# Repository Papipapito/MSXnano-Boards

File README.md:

# MSXnano · Boards

**Proof-of-concept carrier boards for the [MSXnano](https://github.com/Papipapito/MSXnano) project (Sipeed Tang Nano 20K).**
**Placas portadoras de prueba de concepto para el proyecto [MSXnano](https://github.com/Papipapito/MSXnano) (Sipeed Tang Nano 20K).**

*(English below · Español debajo)*

📄 Rich readme / readme enriquecido: [`README.html`](README.html)

### Gallery / Galería

| | |
|:---:|:---:|
|  |  |
| *Top-down 3D · Cenital 3D* | *Tang mounted on the socket · Tang montado en el zócalo* |
|  |  |
| *Assembled · Montado* | *Top copper in KiCad (routing) · Cobre superior en KiCad (rutado)* |

More views in [`dock20k/`](dock20k/): full-res renders, front elevation, bottom copper, schematic & PCB PDFs.
*Más vistas en [`dock20k/`](dock20k/): renders a resolución completa, alzado frontal, cobre inferior, PDFs de esquemático y PCB.*

---

## 🇬🇧 English

These are **proof-of-concept boards built around the Sipeed M0S (BL616)** module. They exist for one exact reason:

> Since **~February 2024**, Sipeed ships Tang Nano 20K boards (silk-marked **`3921`**) whose **on-board BL616** has its **secure-boot eFuse in a state that often prevents it from running the FPGA-Companion firmware**. When that happens, the **USB keyboard and mouse stop working** (HDMI and the on-screen menu still work — that part is the FPGA, not the BL616). Sipeed's official workaround is to use an **external M0S Dock**.

Instead of hanging an external dock off the board with loose wires, these boards **integrate a dedicated M0S (BL616)** as the USB companion — plus a USB hub and WiFi — onto a single carrier, so **everything runs through the Tang's 2×20 headers with no external cables**.

### Boards

| Board | What it is | Status |
|-------|------------|--------|
| [**dock20k**](dock20k/) | Tang Nano 20K carrier: **M0S (BL616)** companion + **FE1.1s** 4-port USB hub (2×USB-A + 2×USB-C) + **ESP32-C6** WiFi (UNAPI). Single USB-C power in. | Schematic ERC 0 · PCB routed (DRC 0) · **not yet fabricated** |
| [**rpi3-compatible**](rpi3-compatible/) | **Raspberry Pi 3 form factor (85×56 mm, 4-layer).** Fully modular: plug-in **Raspberry Pi Pico (RP2040)** USB companion + **ESP-01S** WiFi + **FE1.1s** hub. No soldered BL616/ESP32 — nothing exotic to source. | PCB routed (DRC 0 electrical) · **JLCPCB fab package ready** · not fabricated |

### rpi3-compatible highlights

- **Plug-in Raspberry Pi Pico (RP2040)** as the USB-HID companion, running the FPGA-Companion **`PICO`** build over the same `m0s[]` SPI path — **no RTL changes**, and it sidesteps the Tang `3921` BL616 secure-boot issue entirely (there is no on-board BL616).
- **ESP-01S** for WiFi on the core's **859372 bps** UART. Both the Pico and the ESP are **modules on sockets** — trivial to source, replace, or reflash.
- **Raspberry Pi 3 outline** (85 × 56 mm, RPi3 mounting pattern), **4 copper layers**, routed 100 % with GND planes. Ships with a **complete JLCPCB fab package** (gerbers + BOM + CPL, rotation-corrected).
- Details & key parts: [`rpi3-compatible/README.md`](rpi3-compatible/README.md).

### dock20k highlights

- **M0S (BL616)** runs the stock [FPGA-Companion](https://github.com/MiSTle-Dev/FPGA-Companion) `M0S_DOCK` build over the external `m0s[]` SPI path — **no RTL changes** to the MSXnano core.
- **ESP32-C6-WROOM-1-N8** for internet, running ducasp's [ESP32-UNAPI firmware](https://github.com/ducasp/ESP32-UNAPI-Firmware). It's the C6 (not the classic WROOM) because the core fixes the WiFi UART at **859372 bps**, a rate that is unreliable on the WROOM but fine on the C6.
- Everything routed through the **Tang's own 2×20 headers** — no external cables. Free Tang pins are broken out on an expansion header for future add-ons (e.g. MSX-MIDI).
- Connector & jumper reference: [`dock20k/CONNECTORS.md`](dock20k/CONNECTORS.md).

> ⚠️ **Proof of concept.** Designed and routed in KiCad but **not manufactured or tested in hardware yet.** Before ordering, verify the Tang socket against a physical board (rows at 20.32 mm, pin-1 position).

---

## 🇪🇸 Español

Estas son **placas de prueba de concepto construidas alrededor del módulo Sipeed M0S (BL616)**. Existen por una razón exacta:

> Desde **~febrero de 2024**, Sipeed fabrica placas Tang Nano 20K (marcadas **`3921`** en la serigrafía) cuyo **BL616 de a bordo** tiene el eFuse de **secure-boot en un estado que a menudo le impide ejecutar el firmware FPGA-Companion**. Cuando eso pasa, **el teclado y el ratón USB dejan de funcionar** (el HDMI y el menú en pantalla sí van — eso lo hace la FPGA, no el BL616). La solución oficial de Sipeed es usar un **M0S Dock externo**.

En lugar de colgar un dock externo con cables sueltos, estas placas **integran un M0S (BL616) dedicado** como companion USB —además de un hub USB y WiFi— en una sola portadora, de modo que **todo funciona por los conectores 2×20 del Tang, sin cables externos**.

### Placas

| Placa | Qué es | Estado |
|-------|--------|--------|
| [**dock20k**](dock20k/) | Portadora del Tang Nano 20K: companion **M0S (BL616)** + hub USB **FE1.1s** de 4 puertos (2×USB-A + 2×USB-C) + WiFi **ESP32-C6** (UNAPI). Entrada única de 5 V por USB-C. | Esquemático ERC 0 · PCB rutada (DRC 0) · **sin fabricar aún** |
| [**rpi3-compatible**](rpi3-compatible/) | **Formato Raspberry Pi 3 (85×56 mm, 4 capas).** Totalmente modular: **Raspberry Pi Pico (RP2040)** enchufable como companion USB + **ESP-01S** WiFi + hub **FE1.1s**. Sin BL616/ESP32 soldados — nada raro que abastecer. | PCB rutada (DRC 0 eléctricos) · **paquete de fabricación JLCPCB listo** · sin fabricar |

### Claves de rpi3-compatible

- **Raspberry Pi Pico (RP2040) enchufable** como companion USB-HID, con el build **`PICO`** de FPGA-Companion por la misma ruta SPI `m0s[]` — **sin tocar el RTL**, y esquiva por completo el problema del secure-boot del BL616 de los Tang `3921` (aquí no hay BL616).
- **ESP-01S** para WiFi en la UART del core a **859372 bps**. Tanto el Pico como el ESP son **módulos en zócalos** — fáciles de abastecer, sustituir o reflashear.
- **Contorno Raspberry Pi 3** (85 × 56 mm, patrón de anclajes RPi3), **4 capas de cobre**, rutada al 100 % con planos de GND. Incluye un **paquete de fabricación JLCPCB completo** (gerbers + BOM + CPL, con rotaciones corregidas).
- Detalles y piezas clave: [`rpi3-compatible/README.md`](rpi3-compatible/README.md).

### Claves de dock20k

- El **M0S (BL616)** ejecuta el build `M0S_DOCK` de [FPGA-Companion](https://github.com/MiSTle-Dev/FPGA-Companion) tal cual, por la ruta SPI externa `m0s[]` — **sin tocar el RTL** del core MSXnano.
- **ESP32-C6-WROOM-1-N8** para internet, con el [firmware ESP32-UNAPI](https://github.com/ducasp/ESP32-UNAPI-Firmware) de ducasp. Es el C6 (no el WROOM clásico) porque el core fija la UART del WiFi a **859372 bps**, una velocidad poco fiable en el WROOM pero correcta en el C6.
- Todo enrutado por los **conectores 2×20 del propio Tang** — sin cables externos. Los pines libres del Tang salen a un cabezal de expansión para futuras ampliaciones (p. ej. MSX-MIDI).
- Referencia de conectores y jumpers: [`dock20k/CONNECTORS.md`](dock20k/CONNECTORS.md).

> ⚠️ **Prueba de concepto.** Diseñada y rutada en KiCad pero **aún no fabricada ni probada en hardware.** Antes de encargarla, verifica el zócalo del Tang contra una placa física (filas a 20.32 mm, posición del pin 1).

---

### Credits / Créditos

Board design: **Papipapito**. Third-party footprints/3D models (Sipeed M0S, Espressif ESP32-C6) keep their own licenses. BL616 firmware: [FPGA-Companion](https://github.com/MiSTle-Dev/FPGA-Companion) (MiSTle-Dev). WiFi firmware: [ESP32-UNAPI](https://github.com/ducasp/ESP32-UNAPI-Firmware) (ducasp).

*Diseño de la placa: **Papipapito**. Las huellas/modelos 3D de terceros conservan su licencia. Firmware BL616: FPGA-Companion. Firmware WiFi: ESP32-UNAPI de ducasp.*

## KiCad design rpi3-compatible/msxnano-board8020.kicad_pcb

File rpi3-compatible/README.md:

# rpi3-compatible

**MSXnano carrier in Raspberry Pi 3 form factor (85 × 56 mm), fully modular.**
**Placa portadora MSXnano con formato Raspberry Pi 3 (85 × 56 mm), totalmente modular.**

Instead of soldering the USB companion and WiFi chips (like [`../dock20k`](../dock20k/)), this board takes **plug-in modules**: a **Raspberry Pi Pico (RP2040)** as the USB-HID companion and an **ESP-01S** for WiFi — so there is nothing exotic to source or reflow, and the RPi3 outline drops into any Pi-3 case/mount.

En lugar de soldar los chips de companion USB y WiFi (como en [`../dock20k`](../dock20k/)), esta placa usa **módulos enchufables**: una **Raspberry Pi Pico (RP2040)** como companion USB-HID y un **ESP-01S** para WiFi — así no hay nada raro que abastecer ni soldar, y el contorno RPi3 encaja en cualquier caja/soporte de Pi 3.

### Views / Vistas

| | |
|:---:|:---:|
|  |  |
| *3D top (as placed) · 3D cenital (colocación real)* | *4-layer routing · Rutado 4 capas* |

PDFs: [schematic](board8020_schematic.pdf) · [PCB top](board8020_pcb_top.pdf) · 3D: [`board8020_rpi3.step`](board8020_rpi3.step)

```
USB-C 5V ──fuse 2A──► +5V ──► Tang 5V (socket) + Pico VSYS
                       ├──► AMS1117-3.3 ──► ESP-01S (WiFi)
                       └──► FE1.1s hub ──► 4 downstream ports (500 mA polyfuse each)

Tang (2x20 socket) ──SPI (M0S_* nets)──► RPi Pico (FPGA-Companion PICO build) ──USB host──► FE1.1s hub ──► 2×USB-A + USB2 header
                   ──UART 27/28──► ESP-01S UART @ 859372 bps
Pico GP20 ──► WS2812 header (J8, DIN)
```

## EN — Design notes

- **USB companion = plug-in Raspberry Pi Pico (RP2040)** on a 2×20 female socket, running the FPGA-Companion **`PICO`** build (PIO-USB host). Drives keyboard/mouse/joystick over the same SPI `m0s[]` path the core already detects — **no RTL changes**. Avoids the Tang `3921` BL616 secure-boot problem entirely (no on-board BL616 involved).
- **WiFi = ESP-01S** on a 2×4 female socket, on the core's WiFi UART @ **859372 bps** (its own 3.3 V LDO + pull-ups).
- **Hub = FE1.1s** (SSOP-28) with a **12 MHz SMD-3225 crystal** (JLC Basic C9002). Downstream: 2× USB-A on the rear edge + a **2×5 USB2 header** (2 more ports).
- **Form factor:** exact **Raspberry Pi 3** outline — 85 × 56 mm, 4 mounting holes on the RPi3 58 × 49 pattern. **4 copper layers.**
- **Header-only parts:** the USB2 header (J6), the ESP-01 socket (J7) and the **WS2812 3-pin header (J8)** are left as **plated holes** — solder your own. They are **excluded from the assembly BOM**.

## ES — Notas de diseño

- **Companion USB = Raspberry Pi Pico (RP2040) enchufable** en zócalo 2×20 hembra, con el build **`PICO`** de FPGA-Companion (host USB por PIO). Lleva teclado/ratón/joystick por la misma ruta SPI `m0s[]` que el core ya detecta — **sin tocar el RTL**. Evita por completo el problema del secure-boot del BL616 de los Tang `3921` (aquí no hay BL616).
- **WiFi = ESP-01S** en zócalo 2×4 hembra, en la UART de WiFi del core a **859372 bps** (con su LDO de 3.3 V y pull-ups).
- **Hub = FE1.1s** (SSOP-28) con **cristal 12 MHz SMD-3225** (JLC Basic C9002). Downstream: 2× USB-A en el borde trasero + un **header USB2 2×5** (2 puertos más).
- **Formato:** contorno exacto de **Raspberry Pi 3** — 85 × 56 mm, 4 anclajes en el patrón RPi3 58 × 49. **4 capas de cobre.**
- **Piezas solo-agujeros:** el header USB2 (J6), el zócalo del ESP-01 (J7) y el **header WS2812 de 3 pines (J8)** quedan como **agujeros metalizados** — los sueldas tú. Están **fuera del BOM de montaje**.

## Status / Estado

- EN: 85 × 56 mm **4-layer PCB, routed 100 %** with freerouting, GND planes on all 4 layers. **DRC: 0 unconnected, 0 electrical errors** (only cosmetic silk/library warnings). **JLCPCB fabrication package included** (gerbers + BOM + CPL). Component placement done by hand. **Not fabricated yet** — before ordering, verify the USB-A (J1/J2) and USB-C (J3) footprints/orientation and the Pico/Tang socket rows against physical modules.
- ES: PCB de **4 capas 85 × 56 mm, rutada al 100 %** con freerouting, planos de GND en las 4 capas. **DRC: 0 sin conectar, 0 errores eléctricos** (solo avisos cosméticos de serigrafía/librería). **Paquete de fabricación JLCPCB incluido** (gerbers + BOM + CPL). Colocación de componentes hecha a mano. **Sin fabricar aún** — antes de encargarla, verifica los footprints/orientación de los USB-A (J1/J2) y USB-C (J3) y las filas de los zócalos Pico/Tang contra los módulos físicos.

## Files / Ficheros

`msxnano-board8020.kicad_pro/.kicad_sch/.kicad_pcb` · `sym-lib-table` / `fp-lib-table` (paths via `${KIPRJMOD}`) · `libs/` (M0S + Espressif symbols/footprints/3D, FE1.1s + Tang/Pico sockets custom) · `board8020_schematic.pdf` · `board8020_pcb_top.pdf` · `board8020_rpi3.step` · **fab:** `board8020_gerbers.zip` · `board8020_BOM_jlcpcb.csv` · `board8020_CPL_jlcpcb.csv` (JLCPCB format, top side, rotation-corrected).

## Key parts / Piezas clave (JLCPCB LCSC)

FE1.1s hub `C9359` (SSOP-28) · AMS1117-3.3 `C6186` · USBLC6-2SC6 ESD `C2687116` ×4 · 12 MHz 3225 xtal `C9002` (Basic) · SMAJ5.0A TVS `C2925443` · USB-C `C165948` · USB-A horiz `C2345` ×2 · 10k `C98220` · 5.1k `C23186` · 2.7k `C13167` · PPTC 2A `C960026` / 500mA `C369168`. **Not assembled (holes only):** RPi Pico, Tang Nano 20K, ESP-01S socket, USB2 header, WS2812 header.

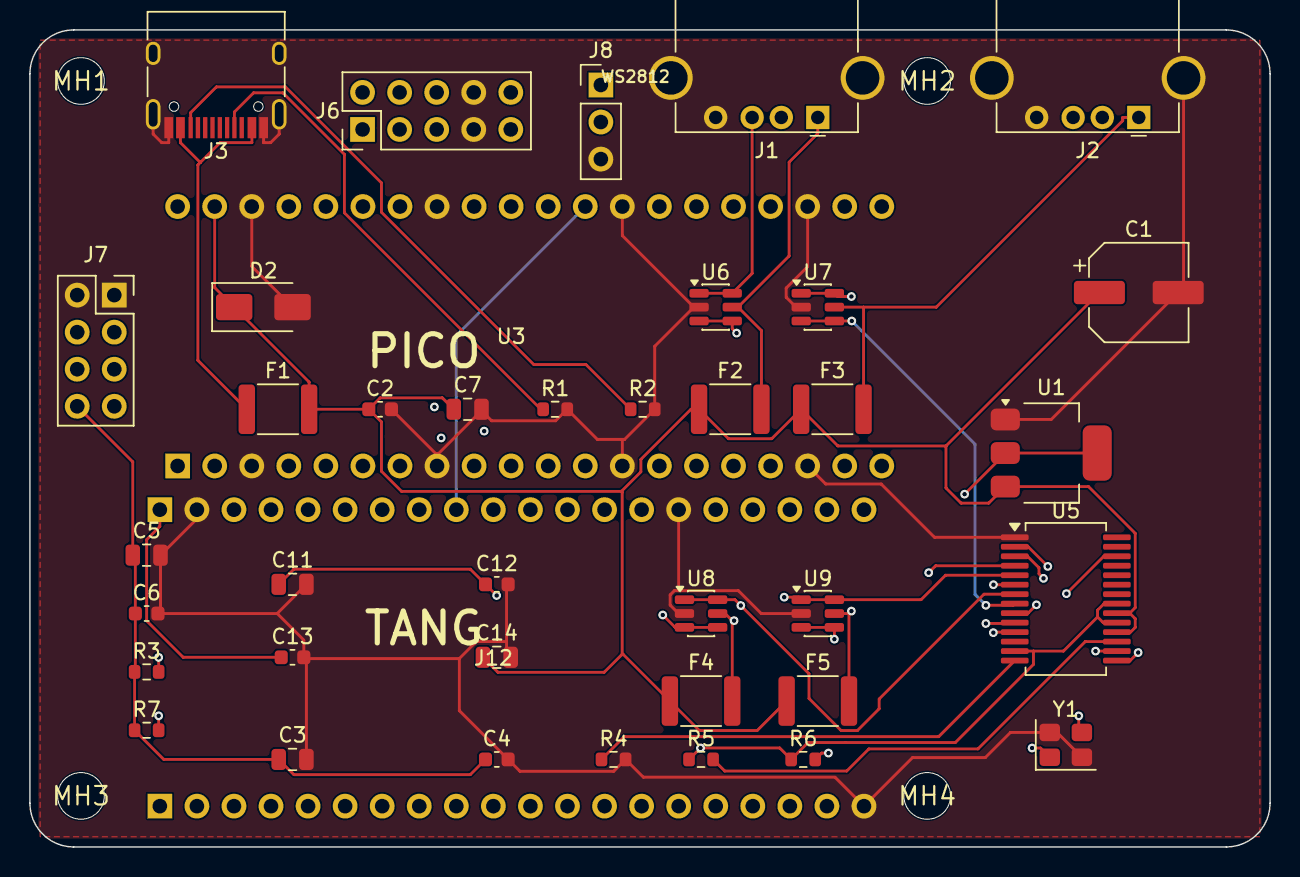
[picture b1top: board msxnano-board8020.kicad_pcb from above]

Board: 4 copper layers, 85.0 x 56.0 mm, 43 parts (0 on the bottom side), 37 nets.

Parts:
C1: 220uF/10V; CP_Elec_6.3x7.7
C2, C4, C6, C12, C13: 100nF; C_0603_1608Metric
C3: 22uF; C_0805_2012Metric
C5, C7, C11, C14: 10uF; C_0805_2012Metric
D2: SMAJ5.0A; D_SMA
F1: 2A; Fuse_1812_4532Metric
F2, F3, F4, F5: 500mA; Fuse_1812_4532Metric
J1: USB-A_front1; USB_A_Stewart_SS-52100-001_Horizontal
J2: USB-A_front2; USB_A_Stewart_SS-52100-001_Horizontal
J3: USB-C_power_in; USB_C_Receptacle_HRO_TYPE-C-31-M-12
J6: USB2.0_Header; PinHeader_2x05_P2.54mm_Vertical
J7: ESP-01S; PinSocket_2x04_P2.54mm_Vertical
J8: WS2812; PinHeader_1x03_P2.54mm_Vertical
J12: TangNano20K; TangNano20K_Socket
MH1, MH2, MH3, MH4: MountingHole_3.2mm
R1, R2: 5k1; R_0603_1608Metric
R3, R5, R6, R7: 10k; R_0603_1608Metric
R4: 2k7 1%; R_0603_1608Metric
U1: AMS1117-3.3; SOT-223-3_TabPin2
U3: RaspberryPi_Pico; RPi_Pico_Socket
U5: FE1.1s; SSOP-28_5.3x10.2mm_P0.65mm
U6, U7, U8, U9: USBLC6-2SC6; SOT-23-6
Y1: 12MHz; Crystal_SMD_3225-4Pin_3.2x2.5mm

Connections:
+3V3_ESP: C3.1, C4.1, C5.1, C6.1, J7.6, J7.8, R3.1, R7.1, U1.2
+3V3_HUB: C11.1, C12.1, R5.1, R6.1, U5.13, U5.19, U5.21
+5V: C1.1, C2.1, C7.1, C13.1, C14.1, D2.1, F1.2, F2.1, F3.1, F4.1, F5.1, J8.1, J12.A1, U1.3, U3.39, U3.40, U5.18, U5.20
BL_USB_DM: U3.5, U5.15
BL_USB_DP: U3.4, U5.16
CC1: J3.A5, R1.1
CC2: J3.B5, R2.1
ESP_GPIO0: J7.3, R3.2
ESP_RST: J7.7, R7.2
ESP_RX0: J7.4, J12.B8
ESP_TX0: J7.5, J12.B9
GND: C1.2, C2.2, C3.2, C4.2, C5.2, C6.2, C7.2, C11.2, C12.2, C13.2, C14.2, D2.2, J1.4, J1.5, J2.4, J2.5, J3.A1, J3.A12, J3.B1, J3.B12, J3.S1, J6.7, J6.8, J7.1, J7.2, J8.3, J12.A2, J12.A15, J12.B20, R1.2, R2.2, R4.2, U1.1, U3.3, U3.8, U3.13, U3.18, U3.23, U3.28, U3.33, U3.38, U5.1, U6.2, U7.2, U8.2, U9.2, Y1.2, Y1.4
HUB_OVCJ: R6.2, U5.26
HUB_REXT: R4.1, U5.14
HUB_RSTJ: R5.2, U5.17
HUB_XIN: U5.3, Y1.1
HUB_XOUT: U5.2, Y1.3
M0S_CSN: J12.A7, U3.22
M0S_IRQ: J12.A9, U3.29
M0S_MISO: J12.A5, U3.21
M0S_MOSI: J12.A6, U3.25
M0S_SCK: J12.A8, U3.24
P1_DM: J1.2, U5.10, U6.3, U6.4
P1_DP: J1.3, U5.11, U6.1, U6.6
P2_DM: J2.2, U5.8, U7.3, U7.4
P2_DP: J2.3, U5.9, U7.1, U7.6
P3_DM: J6.3, U5.6, U8.3, U8.4
P3_DP: J6.5, U5.7, U8.1, U8.6
P4_DM: J6.4, U5.4, U9.3, U9.4
P4_DP: J6.6, U5.5, U9.1, U9.6
TANG_3V3: J12.A16, J12.B19
USB5V_P1: F2.2, J1.1, U6.5
USB5V_P2: F3.2, J2.1, U7.5
USB5V_P3: F4.2, J6.1, U8.5
USB5V_P4: F5.2, J6.2, U9.5
VBUS_IN: F1.1, J3.A4, J3.A9, J3.B4, J3.B9
WS2812_DIN: J8.2, U3.26

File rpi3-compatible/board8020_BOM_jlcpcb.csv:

Comment,Designator,Footprint,LCSC Part #
5.1k 0603 1%,"R1,R2",R_0603,C23186
10k 0603 1%,"R3,R5,R6,R7",R_0603,C98220
2.7k 0603 1%,R4,R_0603,C13167
100nF 50V 0603,"C2,C4,C6,C12,C13",C_0603,C14663
10uF 25V 0805,"C5,C7,C11,C14",C_0805,C15850
22uF 25V 0805,C3,C_0805,C45783
220uF 25V,C1,CP_Elec_6.3x7.7,C2918361
12MHz,Y1,Crystal_SMD_3225-4Pin,C9002
AMS1117-3.3,U1,SOT-223,C6186
FE1.1S,U5,SSOP-28,C9359
USBLC6-2SC6,"U6,U7,U8,U9",SOT-23-6,C2687116
SMAJ5.0A,D2,D_SMA,C2925443
PPTC 2A,F1,Fuse_1812,C960026
PPTC 500mA,"F2,F3,F4,F5",Fuse_1812,C369168
USB-C TYPE-C-31-M-12,J3,USB_C_HRO,C165948
USB-A hembra horiz 902-131A,"J1,J2",USB_A_horiz,C2345

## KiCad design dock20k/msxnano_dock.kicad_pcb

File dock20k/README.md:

# dock20k

Carrier / dock board for the **Tang Nano 20K** running the **MSXnano** core.
Placa portadora ("dock") para el **Tang Nano 20K** con el core **MSXnano**.

📖 See [`CONNECTORS.md`](CONNECTORS.md) for the full connector/jumper reference · [`../README.html`](../README.html) for the illustrated bilingual overview.

### Views / Vistas

| | |
|:---:|:---:|
|  |  |
| *Top-down 3D · Cenital 3D* | *Tang on socket · Tang en zócalo* |
|  |  |
| *Top copper routing (KiCad) · Rutado cobre superior* | *Front elevation of the stack · Alzado del stack* |

Full-res: [`render_top.png`](render_top.png) · [`render_iso_ports.png`](render_iso_ports.png) · [`render_dock.png`](render_dock.png) · [`layout_top.png`](layout_top.png) · [`layout_bottom.png`](layout_bottom.png) · PDFs: [schematic](msxnano_dock_schematic.pdf) · [PCB top](msxnano_dock_pcb_top.pdf) / [bottom](msxnano_dock_pcb_bottom.pdf)

```
USB-C 5V ──fuse 2A──► +5V ──SS34──► Tang 5V pin (J5.1)
                       ├──► AMS1117-3.3 #1 ──► ESP32-C6
                       ├──► AMS1117-3.3 #2 ──► M0S / BL616
                       └──► FE1.1s hub + 4 ports (500 mA polyfuse each)

Tang (2x20 socket) ──SPI 42/41/56/54/51──► M0S BL616 ──USB──► FE1.1s hub ──► 2×USB-A + 2×USB-C
                   ──UART 27/28──► ESP32-C6 UART0 @ 859372 bps
                   ──pin 25──► WS2812   ──pins 15-20──► status LEDs   ──pin 26──► ESP reset (R20 0Ω)
```

## EN — Design notes

- **BL616 = bare Sipeed M0S module** (soldered). Runs the stock FPGA-Companion `M0S_DOCK` build — SPI on IO10–IO14 exactly like the dock, detected by the core via `m0s[2]`. No RTL changes. The M0S has **no on-board regulator** → dedicated 3.3 V LDO.
- **Hub = FE1.1s** (SSOP-28): 12 MHz crystal (load caps integrated), REXT 2.7 kΩ 1%, self-powered (BUSJ→3V3, **OVCJ→10k to 3V3, mandatory**, PWRJ NC). Note: the Rev 1.0 datasheet misprints DMU as pin 25 — it is **pin 15**.
- **WiFi = ESP32-C6-WROOM-1-N8** with ducasp's ESP32-UNAPI firmware. The core's WiFi UART is fixed at **859372 bps**; ducasp reports that rate is unreliable on the classic WROOM but fine on the C6 (the repo's default target). Needs **8 MB flash** → the -N8 part.
- **Rule:** everything goes through the Tang's two 2×20 headers — **no external cables.**

## ES — Notas de diseño

- **BL616 = módulo Sipeed M0S pelado** (soldado). Ejecuta el build `M0S_DOCK` de FPGA-Companion tal cual — SPI en IO10–IO14 igual que el dock, detectado por el core vía `m0s[2]`. Sin tocar RTL. El M0S **no lleva regulador** → LDO de 3.3 V dedicado.
- **Hub = FE1.1s** (SSOP-28): cristal 12 MHz (caps de carga integrados), REXT 2.7 kΩ 1%, self-powered (BUSJ→3V3, **OVCJ→10k a 3V3, obligatorio**, PWRJ sin conectar). Ojo: el datasheet Rev 1.0 imprime mal DMU como pin 25 — es el **pin 15**.
- **WiFi = ESP32-C6-WROOM-1-N8** con el firmware ESP32-UNAPI de ducasp. La UART del WiFi del core está fija a **859372 bps**; ducasp indica que esa velocidad es poco fiable en el WROOM clásico pero correcta en el C6 (target por defecto del repo). Necesita **8 MB de flash** → la variante -N8.
- **Regla:** todo pasa por los dos conectores 2×20 del Tang — **sin cables externos.**

## Status / Estado

- EN: Schematic complete (**ERC 0 errors**). 2-layer PCB, **routed 100%** with freerouting (**DRC 0 errors**), GND pours both sides, RF keepout under the ESP antenna. **Not fabricated yet** — verify the socket against a real Tang (rows 20.32 mm, pin-1 side) before ordering.
- ES: Esquemático completo (**ERC 0 errores**). PCB de 2 capas, **rutada al 100%** con freerouting (**DRC 0 errores**), planos de GND en ambas caras, keepout de RF bajo la antena del ESP. **Sin fabricar aún** — verifica el zócalo contra un Tang real (filas 20.32 mm, lado del pin 1) antes de encargarla.

## Files / Ficheros

`msxnano_dock.kicad_pro/.kicad_sch/.kicad_pcb` · `sym-lib-table` / `fp-lib-table` (paths via `${KIPRJMOD}`) · `libs/` (M0S + Espressif official symbols/footprints/3D, FE1.1s + Tang socket custom) · `msxnano_dock_schematic.pdf` · `msxnano_dock_pcb_top.pdf` / `_bottom.pdf` · `msxnano_dock_bom.csv` · `render_dock.png` / `render_assembled.png`

## Sources / Fuentes (verified 2026-07)

Tang Nano 20K official 3921 schematic + dimensions (dl.sipeed.com) · M0S module & dock schematics + official KiCad footprint · FE1.1s datasheet Rev B (DMU = pin 15) · ESP32-UNAPI source (UART0, baud, 8 MB, targets).

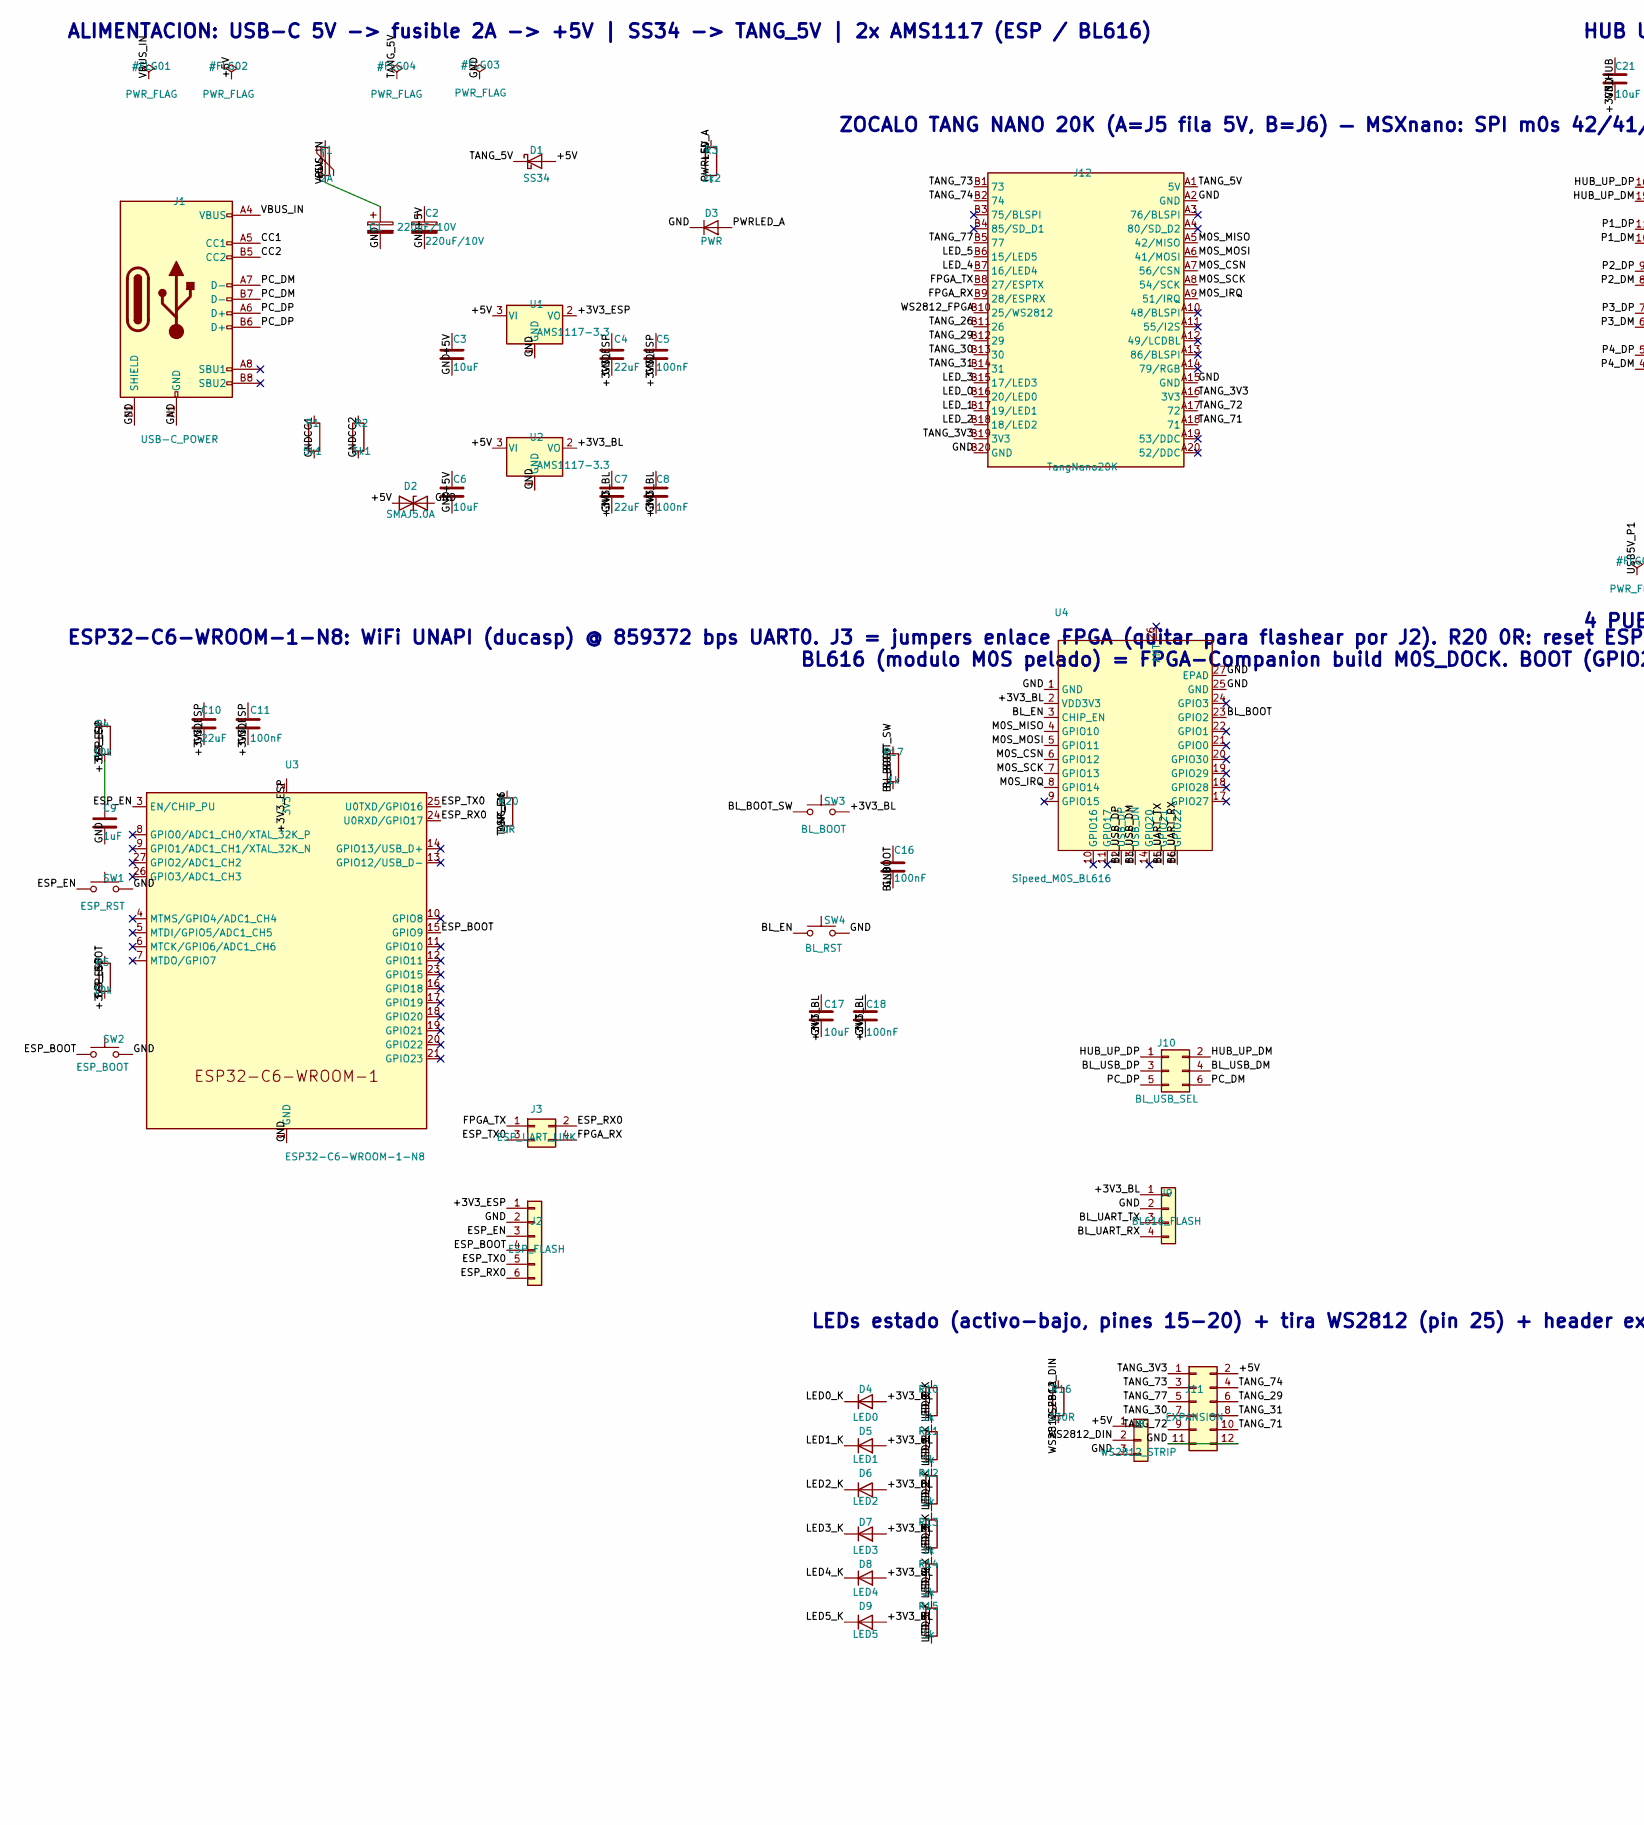
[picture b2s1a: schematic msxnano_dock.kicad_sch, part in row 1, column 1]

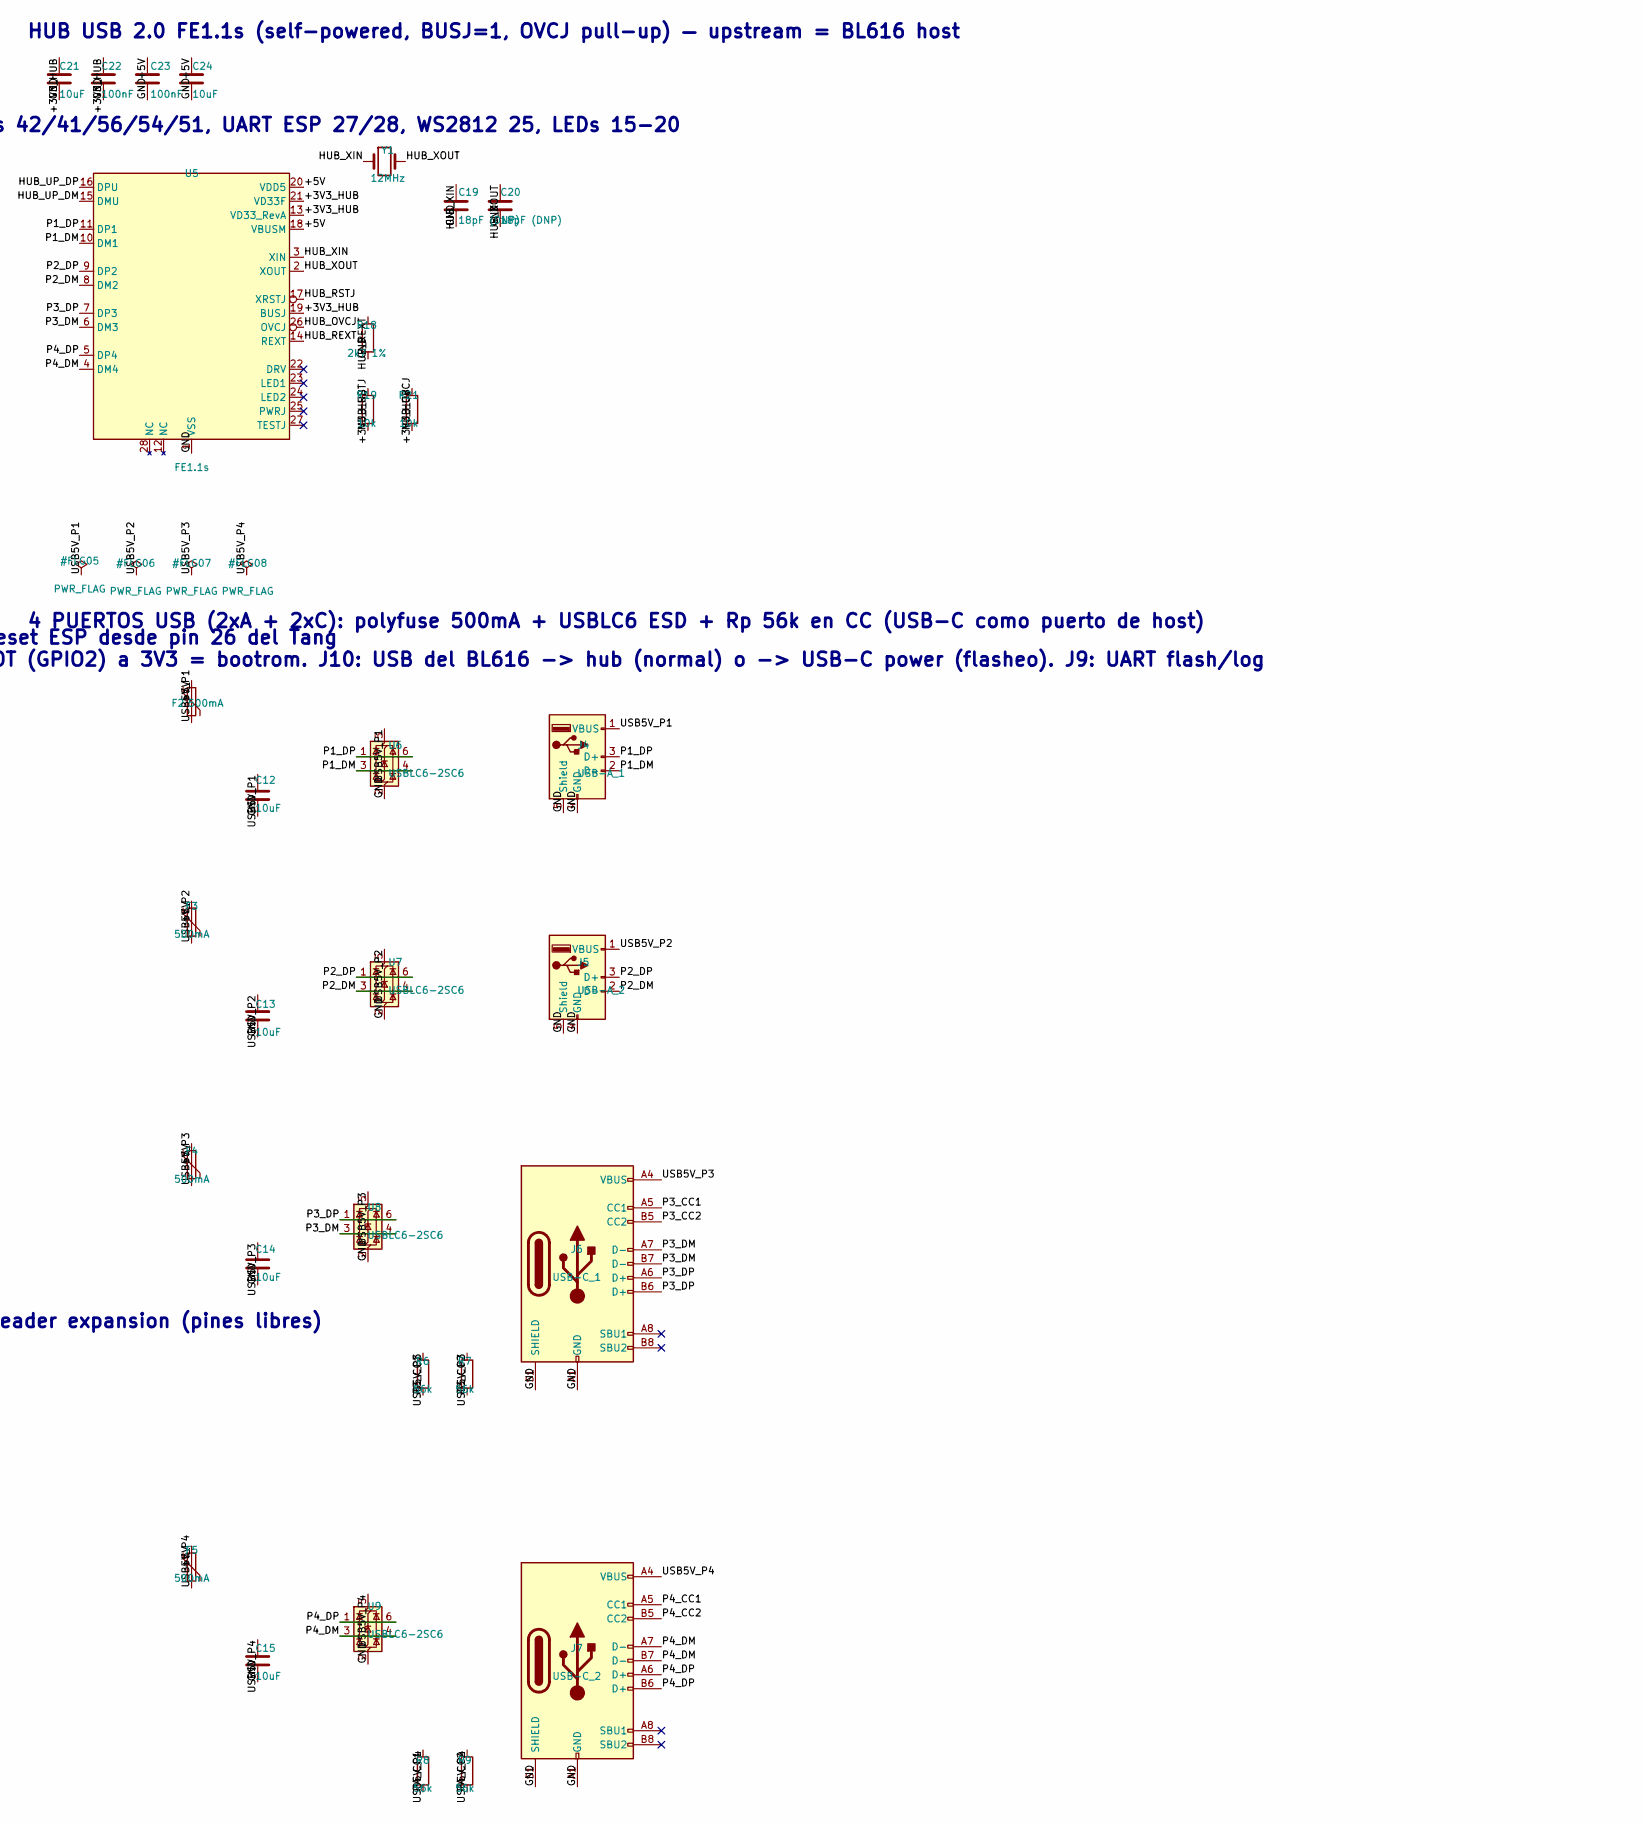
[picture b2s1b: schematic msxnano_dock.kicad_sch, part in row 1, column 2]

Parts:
C1, C2: 220uF/10V; CP_Elec_6.3x7.7
C3, C6, C12, C13, C14, C15, C17, C21, C24: 10uF; C_0805_2012Metric
C4, C7, C10: 22uF; C_0805_2012Metric
C5, C8, C11, C16, C18, C22, C23: 100nF; C_0603_1608Metric
C9: 1uF; C_0603_1608Metric
C19, C20: 18pF (DNP); C_0603_1608Metric
D1: SS34; D_SMA
D2: SMAJ5.0A; D_SMA
D3: PWR; LED_0603_1608Metric
D4: LED0; LED_0603_1608Metric
D5: LED1; LED_0603_1608Metric
D6: LED2; LED_0603_1608Metric
D7: LED3; LED_0603_1608Metric
D8: LED4; LED_0603_1608Metric
D9: LED5; LED_0603_1608Metric
F1: 2A; Fuse_1812_4532Metric
F2, F3, F4, F5: 500mA; Fuse_1812_4532Metric
J1: USB-C_POWER; USB_C_Receptacle_HRO_TYPE-C-31-M-12
J2: ESP_FLASH; PinHeader_1x06_P2.54mm_Vertical
J3: ESP_UART_LINK; PinHeader_2x02_P2.54mm_Vertical
J4: USB-A_1; USB_A_Stewart_SS-52100-001_Horizontal
J5: USB-A_2; USB_A_Stewart_SS-52100-001_Horizontal
J6: USB-C_1; USB_C_Receptacle_HRO_TYPE-C-31-M-12
J7: USB-C_2; USB_C_Receptacle_HRO_TYPE-C-31-M-12
J8: WS2812_STRIP; JST_XH_B3B-XH-A_1x03_P2.50mm_Vertical
J9: BL616_FLASH; PinHeader_1x04_P2.54mm_Vertical
J10: BL_USB_SEL; PinHeader_2x03_P2.54mm_Vertical
J11: EXPANSION; PinHeader_2x06_P2.54mm_Vertical
J12: TangNano20K; TangNano20K_Socket
R1, R2: 5k1; R_0603_1608Metric
R3: 2k2; R_0603_1608Metric
R4, R5, R19, R21: 10k; R_0603_1608Metric
R6, R7, R8, R9: 56k; R_0603_1608Metric
R10, R11, R12, R13, R14, R15, R17: 1k; R_0603_1608Metric
R16: 330R; R_0603_1608Metric
R18: 2k7 1%; R_0603_1608Metric
R20: 0R; R_0603_1608Metric
SW1: ESP_RST; SW_SPST_TL3342
SW2: ESP_BOOT; SW_SPST_TL3342
SW3: BL_BOOT; SW_SPST_TL3342
SW4: BL_RST; SW_SPST_TL3342
U1, U2: AMS1117-3.3; SOT-223-3_TabPin2
U3: ESP32-C6-WROOM-1-N8; ESP32-C6-WROOM-1
U4: Sipeed_M0S_BL616; M0S
U5: FE1.1s; SSOP-28_5.3x10.2mm_P0.65mm
U6, U7, U8, U9: USBLC6-2SC6; SOT-23-6
Y1: 12MHz; Crystal_SMD_HC49-SD

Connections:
+3V3_BL: C7.1, C8.1, C17.1, C18.1, D4.2 (A), D5.2 (A), D6.2 (A), D7.2 (A), D8.2 (A), D9.2 (A), J9.1, SW3.2, U2.2 (VO), U4.2 (VDD3V3)
+3V3_ESP: C4.1, C5.1, C10.1, C11.1, J2.1, R4.1, R5.1, U1.2 (VO), U3.2 (3V3)
+3V3_HUB: C21.1, C22.1, R19.1, R21.1, U5.13 (VD33_RevA), U5.19 (BUSJ), U5.21 (VD33F)
+5V: C1.1, C2.1, C3.1, C6.1, C23.1, C24.1, D1.2 (A), D2.1 (A1), F1.2, F2.1, F3.1, F4.1, F5.1, J8.1, J11.2, R3.1, U1.3 (VI), U2.3 (VI), U5.18 (VBUSM), U5.20 (VDD5)
BL_BOOT: C16.1, R17.1, U4.23 (GPIO2)
BL_BOOT_SW: R17.2, SW3.1
BL_EN: SW4.1, U4.3 (CHIP_EN)
BL_UART_RX: J9.4, U4.16 (GPIO22)
BL_UART_TX: J9.3, U4.15 (GPIO21)
BL_USB_DM: J10.4, U4.13 (USB_DN)
BL_USB_DP: J10.3, U4.12 (USB_DP)
CC1: J1.A5 (CC1), R1.1
CC2: J1.B5 (CC2), R2.1
ESP_BOOT: J2.4, R5.2, SW2.1, U3.15 (GPIO9)
ESP_EN: C9.1, J2.3, R4.2, R20.2, SW1.1, U3.3 (EN/CHIP_PU)
ESP_RX0: J2.6, J3.2, U3.24 (U0RXD/GPIO17)
ESP_TX0: J2.5, J3.3, U3.25 (U0TXD/GPIO16)
FPGA_RX: J3.4, J12.B9 (28/ESPRX)
FPGA_TX: J3.1, J12.B8 (27/ESPTX)
GND: C1.2, C2.2, C3.2, C4.2, C5.2, C6.2, C7.2, C8.2, C9.2, C10.2, C11.2, C12.2, C13.2, C14.2, C15.2, C16.2, C17.2, C18.2, C19.2, C20.2, C21.2, C22.2, C23.2, C24.2, D2.2 (A2), D3.1 (K), J1.A1 (GND), J1.A12 (GND), J1.B1 (GND), J1.B12 (GND), J1.S1 (SHIELD), J2.2, J4.4 (GND), J4.5 (Shield), J5.4 (GND), J5.5 (Shield), J6.A1 (GND), J6.A12 (GND), J6.B1 (GND), J6.B12 (GND), J6.S1 (SHIELD), J7.A1 (GND), J7.A12 (GND), J7.B1 (GND), J7.B12 (GND), J7.S1 (SHIELD), J8.3, J9.2, J11.11, J11.12, J12.A2 (GND), J12.A15 (GND), J12.B20 (GND), R1.2, R2.2, R18.2, SW1.2, SW2.2, SW4.2, U1.1 (GND), U2.1 (GND), U3.1 (GND), U3.28 (GND), U3.29 (GND), U4.1 (GND), U4.25 (GND), U4.27 (EPAD), U5.1 (VSS), U6.2 (GND), U7.2 (GND), U8.2 (GND), U9.2 (GND)
HUB_OVCJ: R21.2, U5.26 (OVCJ)
HUB_REXT: R18.1, U5.14 (REXT)
HUB_RSTJ: R19.2, U5.17 (XRSTJ)
HUB_UP_DM: J10.2, U5.15 (DMU)
HUB_UP_DP: J10.1, U5.16 (DPU)
HUB_XIN: C19.1, U5.3 (XIN), Y1.1
HUB_XOUT: C20.1, U5.2 (XOUT), Y1.2
LED0_K: D4.1 (K), R10.1
LED1_K: D5.1 (K), R11.1
LED2_K: D6.1 (K), R12.1
LED3_K: D7.1 (K), R13.1
LED4_K: D8.1 (K), R14.1
LED5_K: D9.1 (K), R15.1
LED_0: J12.B16 (20/LED0), R10.2
LED_1: J12.B17 (19/LED1), R11.2
LED_2: J12.B18 (18/LED2), R12.2
LED_3: J12.B15 (17/LED3), R13.2
LED_4: J12.B7 (16/LED4), R14.2
LED_5: J12.B6 (15/LED5), R15.2
M0S_CSN: J12.A7 (56/CSN), U4.6 (GPIO12)
M0S_IRQ: J12.A9 (51/IRQ), U4.8 (GPIO14)
M0S_MISO: J12.A5 (42/MISO), U4.4 (GPIO10)
M0S_MOSI: J12.A6 (41/MOSI), U4.5 (GPIO11)
M0S_SCK: J12.A8 (54/SCK), U4.7 (GPIO13)
P1_DM: J4.2 (D-), U5.10 (DM1), U6.3 (I/O2), U6.4 (I/O2)
P1_DP: J4.3 (D+), U5.11 (DP1), U6.1 (I/O1), U6.6 (I/O1)
P2_DM: J5.2 (D-), U5.8 (DM2), U7.3 (I/O2), U7.4 (I/O2)
P2_DP: J5.3 (D+), U5.9 (DP2), U7.1 (I/O1), U7.6 (I/O1)
P3_CC1: J6.A5 (CC1), R6.2
P3_CC2: J6.B5 (CC2), R7.2
P3_DM: J6.A7 (D-), J6.B7 (D-), U5.6 (DM3), U8.3 (I/O2), U8.4 (I/O2)
P3_DP: J6.A6 (D+), J6.B6 (D+), U5.7 (DP3), U8.1 (I/O1), U8.6 (I/O1)
P4_CC1: J7.A5 (CC1), R8.2
P4_CC2: J7.B5 (CC2), R9.2
P4_DM: J7.A7 (D-), J7.B7 (D-), U5.4 (DM4), U9.3 (I/O2), U9.4 (I/O2)
P4_DP: J7.A6 (D+), J7.B6 (D+), U5.5 (DP4), U9.1 (I/O1), U9.6 (I/O1)
PC_DM: J1.A7 (D-), J1.B7 (D-), J10.6
PC_DP: J1.A6 (D+), J1.B6 (D+), J10.5
PWRLED_A: D3.2 (A), R3.2
TANG_3V3: J11.1, J12.A16 (3V3), J12.B19 (3V3)
TANG_5V: D1.1 (K), J12.A1 (5V)
TANG_26: J12.B11 (26), R20.1
TANG_29: J11.6, J12.B12 (29)
TANG_30: J11.7, J12.B13 (30)
TANG_31: J11.8, J12.B14 (31)
TANG_71: J11.10, J12.A18 (71)
TANG_72: J11.9, J12.A17 (72)
TANG_73: J11.3, J12.B1 (73)
TANG_74: J11.4, J12.B2 (74)
TANG_77: J11.5, J12.B5 (77)
USB5V_P1: C12.1, F2.2, J4.1 (VBUS), U6.5 (VBUS)
USB5V_P2: C13.1, F3.2, J5.1 (VBUS), U7.5 (VBUS)
USB5V_P3: C14.1, F4.2, J6.A4 (VBUS), J6.A9 (VBUS), J6.B4 (VBUS), J6.B9 (VBUS), R6.1, R7.1, U8.5 (VBUS)
USB5V_P4: C15.1, F5.2, J7.A4 (VBUS), J7.A9 (VBUS), J7.B4 (VBUS), J7.B9 (VBUS), R8.1, R9.1, U9.5 (VBUS)
VBUS_IN: F1.1, J1.A4 (VBUS), J1.A9 (VBUS), J1.B4 (VBUS), J1.B9 (VBUS)
WS2812_DIN: J8.2, R16.2
WS2812_FPGA: J12.B10 (25/WS2812), R16.1

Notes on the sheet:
ALIMENTACION: USB-C 5V -> fusible 2A -> +5V | SS34 -> TANG_5V | 2x AMS1117 (ESP / BL616)
ZOCALO TANG NANO 20K (A=J5 fila 5V, B=J6) — MSXnano: SPI m0s 42/41/56/54/51, UART ESP 27/28, WS2812 25, LEDs 15-20
HUB USB 2.0 FE1.1s (self-powered, BUSJ=1, OVCJ pull-up) — upstream = BL616 host
ESP32-C6-WROOM-1-N8: WiFi UNAPI (ducasp) @ 859372 bps UART0. J3 = jumpers enlace FPGA (quitar para flashear por J2). R20 0R: reset ESP desde pin 26 del Tang
BL616 (modulo M0S pelado) = FPGA-Companion build M0S_DOCK. BOOT (GPIO2) a 3V3 = bootrom. J10: USB del BL616 -> hub (normal) o -> USB-C power (flasheo). J9: UART flash/log
4 PUERTOS USB (2xA + 2xC): polyfuse 500mA + USBLC6 ESD + Rp 56k en CC (USB-C como puerto de host)
LEDs estado (activo-bajo, pines 15-20) + tira WS2812 (pin 25) + header expansion (pines libres)

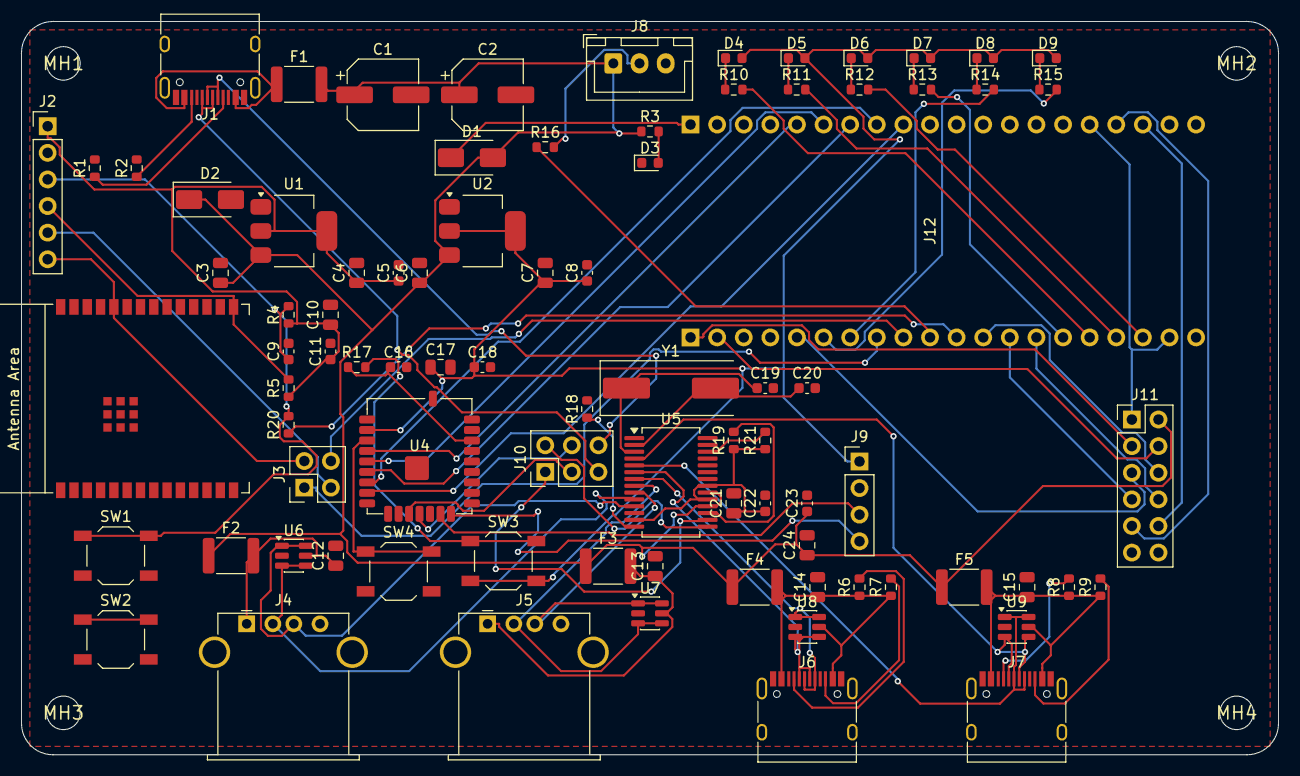
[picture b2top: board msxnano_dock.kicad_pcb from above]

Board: 2 copper layers, 120.0 x 70.0 mm, 89 parts (0 on the bottom side), 77 nets.

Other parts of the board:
MH1, MH2, MH3, MH4: MountingHole_3.2mm

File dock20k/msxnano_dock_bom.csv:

value,footprint,quantity,references
12MHz,Crystal:Crystal_SMD_HC49-SD,1,['Y1']
MountingHole_3.2mm,MountingHole:MountingHole_3.2mm,4,"['MH4', 'MH1', 'MH3', 'MH2']"
LED2,LED_SMD:LED_0603_1608Metric,1,['D6']
1k,Resistor_SMD:R_0603_1608Metric,7,"['R17', 'R14', 'R11', 'R10', 'R13', 'R12', 'R15']"
SS34,Diode_SMD:D_SMA,1,['D1']
EXPANSION,Connector_PinHeader_2.54mm:PinHeader_2x06_P2.54mm_Vertical,1,['J11']
BL_USB_SEL,Connector_PinHeader_2.54mm:PinHeader_2x03_P2.54mm_Vertical,1,['J10']
18pF (DNP),Capacitor_SMD:C_0603_1608Metric,2,"['C19', 'C20']"
2A,Fuse:Fuse_1812_4532Metric,1,['F1']
330R,Resistor_SMD:R_0603_1608Metric,1,['R16']
220uF/10V,Capacitor_SMD:CP_Elec_6.3x7.7,2,"['C1', 'C2']"
10uF,Capacitor_SMD:C_0805_2012Metric,9,"['C21', 'C13', 'C3', 'C15', 'C24', 'C12', 'C6', 'C14', 'C17']"
ESP_RST,Button_Switch_SMD:SW_SPST_TL3342,1,['SW1']
22uF,Capacitor_SMD:C_0805_2012Metric,3,"['C10', 'C7', 'C4']"
ESP_BOOT,Button_Switch_SMD:SW_SPST_TL3342,1,['SW2']
5k1,Resistor_SMD:R_0603_1608Metric,2,"['R1', 'R2']"
100nF,Capacitor_SMD:C_0603_1608Metric,7,"['C8', 'C16', 'C23', 'C22', 'C11', 'C18', 'C5']"
SMAJ5.0A,Diode_SMD:D_SMA,1,['D2']
56k,Resistor_SMD:R_0603_1608Metric,4,"['R9', 'R7', 'R6', 'R8']"
LED1,LED_SMD:LED_0603_1608Metric,1,['D5']
LED3,LED_SMD:LED_0603_1608Metric,1,['D7']
FE1.1s,Package_SO:SSOP-28_5.3x10.2mm_P0.65mm,1,['U5']
BL_RST,Button_Switch_SMD:SW_SPST_TL3342,1,['SW4']
TangNano20K,msxnano_dock:TangNano20K_Socket,1,['J12']
PWR,LED_SMD:LED_0603_1608Metric,1,['D3']
LED5,LED_SMD:LED_0603_1608Metric,1,['D9']
10k,Resistor_SMD:R_0603_1608Metric,4,"['R19', 'R4', 'R5', 'R21']"
BL_BOOT,Button_Switch_SMD:SW_SPST_TL3342,1,['SW3']
USB-A_1,Connector_USB:USB_A_Stewart_SS-52100-001_Horizontal,1,['J4']
500mA,Fuse:Fuse_1812_4532Metric,4,"['F2', 'F5', 'F3', 'F4']"
0R,Resistor_SMD:R_0603_1608Metric,1,['R20']
USB-C_2,Connector_USB:USB_C_Receptacle_HRO_TYPE-C-31-M-12,1,['J7']
LED4,LED_SMD:LED_0603_1608Metric,1,['D8']
USBLC6-2SC6,Package_TO_SOT_SMD:SOT-23-6,4,"['U7', 'U6', 'U9', 'U8']"
USB-C_1,Connector_USB:USB_C_Receptacle_HRO_TYPE-C-31-M-12,1,['J6']
2k7 1%,Resistor_SMD:R_0603_1608Metric,1,['R18']
LED0,LED_SMD:LED_0603_1608Metric,1,['D4']
WS2812_STRIP,Connector_JST:JST_XH_B3B-XH-A_1x03_P2.50mm_Vertical,1,['J8']
USB-A_2,Connector_USB:USB_A_Stewart_SS-52100-001_Horizontal,1,['J5']
USB-C_POWER,Connector_USB:USB_C_Receptacle_HRO_TYPE-C-31-M-12,1,['J1']
1uF,Capacitor_SMD:C_0603_1608Metric,1,['C9']
BL616_FLASH,Connector_PinHeader_2.54mm:PinHeader_1x04_P2.54mm_Vertical,1,['J9']
ESP_FLASH,Connector_PinHeader_2.54mm:PinHeader_1x06_P2.54mm_Vertical,1,['J2']
AMS1117-3.3,Package_TO_SOT_SMD:SOT-223-3_TabPin2,2,"['U2', 'U1']"
ESP_UART_LINK,Connector_PinHeader_2.54mm:PinHeader_2x02_P2.54mm_Vertical,1,['J3']
2k2,Resistor_SMD:R_0603_1608Metric,1,['R3']
ESP32-C6-WROOM-1-N8,msxnano_dock:ESP32-C6-WROOM-1,1,['U3']
Sipeed_M0S_BL616,msxnano_dock:M0S,1,['U4']
